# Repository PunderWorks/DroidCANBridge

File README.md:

# DroidCANBridge

A very small, inexpensive CAN-to-UART bridge for droid builders: it translates CAN bus frames to a
standard UART and back, so droid components without CAN support can join a CAN network.

- **MCU:** STM32C092 (TSSOP-20), with a built-in CAN FD controller
- **CAN:** CAN FD-capable transceiver (classic CAN 2.0 in firmware for now); two 3-pin JST-XH connectors
  (1 GND, 2 CANL, 3 CANH, the PunderWorks CAN standard) for daisy-chaining, and a jumper for the 120 Ω
  termination resistor. The CAN ground wire is optional; on the board it reaches GND through a
  resettable fuse, so it can never carry a load's return current
- **UART:** 2-pin JST-XH connector (RX, TX) with a jumper that sets the logic level to 3.3 V or 5 V
- **Power:** 5 V in on a WAGO terminal (reverse-polarity protected), with a WAGO passthrough output
- **Programming:** standard 6-pin FTDI header using the STM32's built-in serial bootloader, with
  DTR auto-reset and a boot button

Status: PCB complete (50 x 40 mm, two layers): routed, silkscreen and graphics done (PunderWorks
logo and a QR code to this repo on the back); not yet ordered. Gerbers, drills, BOM and placement
are in [`PCB/production/`](PCB/production/). Hardware is in [`PCB/`](PCB/) (see
[PCB/README.md](PCB/README.md) for requirements and design decisions); firmware will live in `src/`.

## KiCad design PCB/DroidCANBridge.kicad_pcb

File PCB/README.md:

# DroidCANBridge hardware

The electrical design is Stackup KDL in [`stackup/`](stackup/) (`board.kdl`, plus the local parts in
`parts.kdl`). The KiCad board `DroidCANBridge.kicad_pcb` is synced from it through
`DroidCANBridge.stackup_sch`. Manufacturer datasheets are in [`datasheets/`](datasheets/), with
their source URLs and hashes in `datasheets/manifest.json`.

```sh
stackup check PCB/stackup/board.kdl --locked     # check the design
```

After changing the KDL, use **Sync PCB from stackup** in KiCad's PCB editor, or sync headless with
the board closed:

```sh
/Applications/KiCad/KiCad.app/Contents/Frameworks/Python.framework/Versions/Current/bin/python3 \
  <stackup checkout>/kicad-plugin/sync_headless.py PCB/DroidCANBridge.kicad_pcb
```

Commit the synced PCB with the KDL. CI fails if syncing would change the committed PCB.

## Requirements

| Area | Requirement |
|---|---|
| Size | As small as possible. M3 mounting holes. No target outline. |
| Assembly | SMD parts assembled by JLCPCB. Connectors, terminals and headers are through-hole, hand-soldered. |
| MCU | Inexpensive STM32 with a CAN FD controller. |
| CAN | PunderWorks CAN standard (reference design DroidPowerSense v1): two 3-pin JST-XH connectors (daisy-chain in/out), pinout `1 CAN_GND, 2 CANL, 3 CANH`, printed on the silkscreen. CAN_GND to board GND through a PTC. Jumper-selectable 120 Ω termination. No power on the CAN connector. No ESD protection beyond the transceiver's own. |
| UART | One 2-pin JST-XH connector, pinout `RX, TX` (named from this board's side). Works with 3.3 V and 5 V devices, selected by a pin jumper. |
| Power | 5 V in on a through-hole WAGO terminal, with reverse-polarity protection. A second WAGO terminal passes the 5 V input through to the connected device. No fuse. |
| Programming | Standard 6-pin FTDI header (`GND, CTS, VCC, TX, RX, DTR`) on the STM32 system-bootloader UART. The board can run from the FTDI header's VCC on the bench. DTR drives reset. A small boot button selects the bootloader. |
| Indicators | None (status is reported over serial). |

## Circuit

| Block | Parts | Notes |
|---|---|---|
| Power in | J_PWR_IN, J_PWR_OUT (WAGO 2601-1102), D_IN, D_FTDI (SS14), C_VSYS | The two SS14s OR the WAGO input and the FTDI VCC onto VSYS. D_IN is the reverse-polarity protection. Each diode stops one source back-feeding the other, so the FTDI never powers the passthrough terminal. |
| 3.3 V | ldo (AP2112K-3.3) | VSYS → +3V3 for everything on the board. |
| MCU | mcu (STM32C092FCP6, TSSOP-20) | 100 nF + 4.7 µF on VDD; 100 nF NRST filter. |
| CAN | can_xcvr (TCAN334GDR), J_CAN1/J_CAN2, F_CAN_GND, R_TERM + J_TERM | STB/SHDN left on their internal pull-downs (normal mode). Connectors: pin 1 CAN_GND, 2 CANL, 3 CANH. CAN_GND runs straight from J_CAN1 to J_CAN2 (the bus ground daisy-chains) and reaches board GND through F_CAN_GND (Bourns MF-NSMF020X-2, 1206). Fit the TERM shunt at the ends of the bus. |
| Device UART | J_UART, J_VIO, R_TXPU, Q_RX (BSS138), R_RXPU | TX: open-drain with a 1 kΩ pull-up to the jumper-selected level. RX: BSS138 level shifter. |
| FTDI | J_FTDI, C_DTR, D_NRST (BAT54S) | DTR is AC-coupled to NRST (Arduino-style auto-reset); the BAT54S clamps NRST between GND and +3V3. CTS is tied to GND. |
| Boot | SW_BOOT (TS-1187A), R_BOOT | Hold SW_BOOT through a reset to enter the bootloader. No SWD pads: the FTDI header is the only programming path. |

Jumpers: **J_VIO** shunt on 1-2 = 3.3 V UART, 2-3 = 5 V UART (VSYS). **J_TERM** shunt fitted = 120 Ω
terminator in. The two shunts (SH_VIO, SH_TERM: Würth 60900213421) are BOM-only parts with
outline-only footprints, so they are on the BOM but not in the placement file.

## Layout

The board is 50 x 40 mm, two layers, laid out for how it sits in a droid harness, with
power and signals flowing left to right:

| Edge | Connectors |
|---|---|
| Left (in) | J_PWR_IN (WAGO, wires enter from the left), J_CAN1 |
| Right (out) | J_PWR_OUT (WAGO, wires leave to the right), J_CAN2, J_UART |
| Bottom | J_FTDI, lying along the edge, pin 1 (GND) on the left |

- Both WAGOs have **+5V on the top pole and GND on the bottom**. J_PWR_OUT is turned the opposite
  way from J_PWR_IN, which reverses its pin order, so its +5V is pin 2 (see `board.kdl`). Mark + and
  − on the silkscreen beside both.
- The CAN connectors are turned opposite ways: J_CAN1 reads CANH, CANL, CAN_GND from the top
  (pin 1 at the bottom) and J_CAN2 reads CAN_GND, CANL, CANH (pin 1 at the top). Each pin has an
  edge label (H, L, G) beside it. J_UART has pin 1 (RX) at the top.
- J_CAN2 sits between the 5V OUT WAGO and J_UART, with 1.1 mm and 1.4 mm between the bodies, so its
  "CAN OUT" label runs vertically to its left (0.8 mm-wide characters, as on the FTDI pins).
- CAN_GND: J_CAN1 pin 1 to F_CAN_GND (beside TERM) on the top, and a 0.5 mm track on the bottom
  from J_CAN1 pin 1, under the FTDI header, up to J_CAN2 pin 1. F_CAN_GND's other pad joins the
  top GND pour.
- The +5V passthrough runs straight across the top edge between the WAGOs, above the OR diodes and
  LDO. Size it for the passthrough current, not the board's own < 100 mA.
- The WAGO levers overhang the side edges by about 2 mm (WAGO drawing: 16.58 mm with the lever
  against the 14.5 mm body).
- Two M3 holes in opposite corners: H1 bottom-left, H2 top-right (above J_PWR_OUT). Each has a
  3.5 mm-radius copper keep-out on both layers (rule areas `Keepout H1/H2`), so screw heads,
  washers and standoffs sit on bare board, not on the GND pour.
- GND pours fill both layers. The bottom one gives the passthrough's return a solid path under the
  3 mm +5V_IN track. Pads join them through thermal reliefs with 0.5 mm spokes, wide enough for the
  WAGO GND pins and still easy to hand-solder. 26 GND stitching vias (0.8/0.4 mm) around the
  perimeter and through open areas tie the two pours together, plus vias joining top-pour pockets
  that tracks enclose.
- Silkscreen: reference designators and values are hidden (they remain on the Fab layer for
  assembly drawings). The top labels each connector, jumper setting and the boot button, and the
  FTDI pins from the cable's side (GND, CTS, VCC, RXI, TXO, DTR). The back carries the PunderWorks
  logo (`PunderWorks_Logo_14mm`, a board-only footprint in `libraries/DroidCANBridge.pretty`,
  copied from DroidPowerSense with its source image in `libraries/logos/`), the board name and
  version, the repo URL, and a 6.2 mm QR code to github.com/PunderWorks/DroidCANBridge.
- `scripts/pcb/place.py` produced the starting placement. Once the board is edited in KiCad, the
  board file is the source of truth.

## GPIO table (STM32C092FCP6, TSSOP-20)

From DS14720 Rev 2, Figure 3 and Table 12. Pads marked "shared" bond several die pins together;
firmware must leave the unused ones in their reset (analog) state.

| Pad | Pin (shared) | Net | Function | Notes |
|---|---|---|---|---|
| 1 | PB7 (PB8) | UART_RX_3V3 | USART1_RX | From Q_RX; 1 kΩ pull-up on board. |
| 2 | PC14 | — | spare | |
| 3 | PC15 | — | spare | |
| 4 | VDD/VDDA | +3V3 | supply | |
| 5 | VSS/VSSA | GND | supply | |
| 6 | PF2-NRST | NRST | reset | Bidirectional reset (factory NRST_MODE = 11). DTR auto-reset. |
| 7, 8 | PA0, PA1 | — | spare | |
| 9 | PA2 | FTDI_RXD | USART2_TX | Bootloader USART (AN2606 Table 19). |
| 10 | PA3 | FTDI_TXD | USART2_RX | Bootloader USART. |
| 11-14 | PA4-PA7 | — | spare | Bootloader SPI1 pins (pulled down in bootloader mode); unused here. |
| 15 | PA8 (PB0, PB1, PB2) | — | spare | |
| 16 | PA11 (PA9) | CAN_RX | FDCAN1_RX | Bootloader remaps USART1_TX here but holds it in reset state until 0x7F arrives on pad 17. |
| 17 | PA12 (PA10) | CAN_TX | FDCAN1_TX | Bootloader remaps USART1_RX here (input, pull-up). Only the transceiver's TXD input is on it. |
| 18 | PA13 | — | spare (SWDIO) | Not brought out; no SWD on this board. |
| 19 | PA14-BOOT0 (PA15) | BOOT0 | BOOT0 | 10 kΩ pull-down + SW_BOOT to +3V3. BOOT0 only once nBOOT_SEL is cleared (see Firmware). |
| 20 | PB6 (PB3, PB4, PB5) | UART_TX | USART1_TX | Open-drain, internal pull off (pin sees up to 5.25 V). Bootloader I2C1_SCL. |

## DC operating points

Supply states: WAGO only, FTDI only, both, and the bridge unpowered with the UART device powered.

| Node | Value | Limit (source) | OK |
|---|---|---|---|
| +5V_IN | 4.75-5.25 V (stated ±5%) | SS14 VRRM 40 V | ✓ |
| FTDI_VCC | 4.4-5.25 V (USB at the device) | SS14 VRRM 40 V | ✓ |
| VSYS | 3.85-5.25 V (input less ≤ 0.55 V, SS14 VF at 1 A; < 0.4 V typical at this current) | AP2112 VIN 2.5-6 V; needs ≥ 3.5 V (3.3 V + 200 mV max dropout at 300 mA, AP2112 table p. 8) | ✓ |
| +3V3 | 3.25-3.35 V (±1.5%) | STM32 2.0-3.6 V; TCAN334 3.0-3.6 V | ✓ |
| +3V3 load | ≤ 85 mA (TCAN334 70 mA dominant + MCU budget 15 mA) | AP2112 600 mA | ✓ |
| LDO dissipation | ≤ (5.25 - 3.25) V × 85 mA = 0.17 W | SOT-23-5; check the board temperature on the bench | ✓ |
| UART_TX low | sinking ≤ 5.25 mA (VIO / 1 kΩ) | VOL ≤ 0.4 V at 8 mA (DS14720 Table 51) | ✓ |
| UART_TX high, 5 V setting | 3.85-5.25 V | ATmega VIH 0.6 × VCC = 3.0 V at 5 V (from memory, typical AVR); PB6 FT max VDD + 4.0 V = 7.25 V (Table 21) | ✓ |
| Q_RX on (device TX low ≤ 0.8 V) | VGS ≥ 3.25 - 0.8 = 2.45 V | BSS138 VGS(th) max 1.5 V (onsemi, electrical characteristics) | ✓ |
| UART_RX_3V3, device low | ≤ 0.8 V + 3.3 mA × RDS(on) (≤ 6 Ω at 4.5 V; more at 2.45 V) ≈ 0.85 V | VIL 0.3 × VDD = 0.98 V (Table 50) | ✓ (assumes device VOL ≤ 0.8 V; typical ≤ 0.4 V) |
| UART_RX_3V3, device high | 3.25 V via R_RXPU | VIH 0.7 × VDD = 2.31 V | ✓ |
| UART_RX_3V3, bridge unpowered | ≈ 0 V (FET off, body diode reverse-biased) | FT pin max 4.0 V with VDD = 0 (Table 21) | ✓ |
| BOOT0 at rest / pressed | 0 V / 3.3 V (0.33 mA) | VIL 0.98 V / VIH 2.31 V | ✓ |
| NRST on DTR fall, 3.3 V cable | 3.3 - 3.3 × 1 µF/1.1 µF = 0.3 V, below VIL for 7-16 ms (τ = 1.1 µF × RPU 25-55 kΩ) | VIL(NRST) 0.3 × VDD = 0.98 V; filter 70 ns (Table 53) | ✓ |
| NRST on DTR fall, 5 V cable | clamped by BAT54S to -0.35 to -0.52 V, below VIL for 12-27 ms (SPICE) | MCU negative injection ≤ 5 mA (Table 22): simulated ≤ 0.25 mA; without the BAT54S, 26 mA | ✓ |
| NRST on DTR rise (port close) | ≤ 4.32 V with the BAT54S (SPICE); 7.9 V without it | VIN ≤ VDD + 4.0 V = 7.3 V (Table 21) | ✓ |
| CAN terminator | 2-3 V differential across 120 Ω → ≤ 75 mW | 0805 125 mW | ✓ |
| CAN_GND to GND, normal | ~0 A (≈ 1 mA signal reference at most), ≤ 3.3 Ω (R1max) → ≤ 3.3 mV | Ihold 0.20 A at 23 °C, 0.10 A at 85 °C (MF-NSMF pp. 1, 3) | ✓ |
| CAN_GND to GND, fault | WAGO GND lost with a CAN cable fitted: this board's < 100 mA plus the passthrough load's return (≤ 10 A, the WAGO rating; no upstream fuse) through the PTC until it trips; then ~0.6 W tripped at ≤ 5.25 V | Vmax 30 V (5.7× the 5.25 V max), Imax 60 A, trips in ≤ 0.6 s at 1.0 A (MF-NSMF p. 1); JST-XH contact 3 A | ✓ |

## Firmware requirements from the hardware

- **First flash: clear nBOOT_SEL over the UART before writing any firmware.** Factory option bytes
  are nBOOT_SEL = 1, nBOOT0 = 1 (RM0490 p. 66), so a fresh part ignores the BOOT0 pin and reaches
  the bootloader only through the empty-flash check (RM0490 Table 9, §3.1.4). There are no SWD pads,
  so if firmware were written first with nBOOT_SEL still set, the chip would always boot from flash
  and only that firmware could get back to the bootloader. On the blank chip, connect the FTDI
  and run `STM32_Programmer_CLI -c port=<tty> -ob nBOOT_SEL=0` (STM32CubeProgrammer talks to the ROM
  bootloader over UART and can write option bytes). From then on, holding SW_BOOT through a reset
  always reaches the bootloader, whatever the firmware does. Firmware should also check the bit at
  startup and clear it if a board somehow skipped the step.
- **PB6 (UART TX):** open-drain alternate function, internal pull-up and pull-down off (required to
  sustain more than 4 V, DS14720 Table 21 note 2).
- **PB7 (UART RX):** no internal pull needed (R_RXPU).
- **FDCAN (PunderWorks CAN standard):** classic CAN 2.0 frame format with FD mode off, not just a
  matching data rate, and payloads of at most 8 bytes. One bit rate across the bus, set by the
  motor controllers, with the sample point at ~87.5% (match it on every node). Enable protocol
  exception handling too, so a stray FD frame is ignored instead of answered with error frames.
  The hardware stays FD-capable, so a later move to FD is firmware and segmenting only.
- **Shared pads:** leave PB8, PB0-PB2, PA9, PA10, PA15, PB3-PB5 untouched (analog). Use the SYSCFG
  remap only if the pad assignment changes.
- **Flashing:** the ROM bootloader on USART2 (8 data bits, even parity, 1 stop bit; AN2606 Table 19).
  Hold SW_BOOT, let the flasher pulse DTR, release after it connects.

## Decisions

- **STM32C092FCP6 (TSSOP-20).** The cheapest STM32 with FDCAN (the C091 has none). No STM32 comes in a
  through-hole package, so the MCU is SMD; once JLCPCB is assembling it, the other small parts are SMD
  too to keep the board compact. The library part only has LQFP packages, so `parts.kdl` carries a
  TSSOP-20 copy (candidate to upstream). JLCPCB stock is low (C44847704, 6 pcs on 2026-11-05;
  Mouser 3,314), so recheck before ordering and plan on global sourcing or consigned parts.
- **Pin plan.** FTDI on USART2 PA2/PA3 because that is a bootloader USART bonded on TSSOP-20 (the other,
  USART1 on PA9/PA10, is remapped onto pads 16/17 there). CAN on pads 16/17. Device UART on USART1
  PB6/PB7 (pads 20/1). The bootloader's I2C1 on PB6/PB7 cannot trigger: SCL (PB6) never toggles with
  the MCU in the bootloader. Its FDCAN bootloader is not available on TSSOP-20 (AN2606 Table 19 note 2).
- **PunderWorks CAN standard (2026-11-17).** All PunderWorks CAN boards match DroidPowerSense v1:
  3-pin JST-XH (1 CAN_GND, 2 CANL, 3 CANH), TCAN334GDR, CAN_GND daisy-chained between the two
  connectors and tied to GND through a PTC, 120 Ω on a TERM jumper with a Würth
  60900213421 shunt, and no power on the CAN connector. This board was brought into line before
  it was ever made, so it stays V1.0. It replaces the earlier 2-pin connectors with no ground,
  which relied on every board sharing ground through the power wiring. A bus ground wire keeps
  nodes within the transceiver's common-mode range when they are powered separately. Without the
  PTC, losing this board's WAGO GND with a CAN cable still fitted would send the downstream
  device's return current through a 3 A JST contact and signal wire. The shunt is
  DroidPowerSense's. The builder may leave out the CAN_GND wire.
- **CAN_GND PTC: Bourns MF-NSMF020X-2, 1206 (2026-11-18).** The standard leaves the PTC to each
  board. DroidPowerSense's MF-MSMF014/60X-2 (60 V, 1812) is sized for a 32 V battery rail and
  isn't stocked at LCSC, so this 5 V board uses a 1206: Vmax 30 V, Imax 60 A, Ihold 0.20 A
  (0.10 A at 85 °C), R1max 3.3 Ω (MF-NSMF p. 1, p. 3). Imax covers the worst case, the passthrough
  load's return bounded only by the 10 A WAGO since there is no upstream fuse. Ihold is far
  above the ≈ 1 mA reference current and the trip current (0.40 A) well under the 3 A JST
  contact. Footprint `DroidCANBridge:Bourns_MF-NSMF_1206_Style2` from the p. 8 pad layout
  (1.0 × 1.6 mm pads, 2.0 mm gap). Stock on 2026-11-18: Mouser 11,420, DigiKey 28,416, LCSC
  9,850 (C210358, JLCPCB Extended). Rejected: MF-NSMF020 (non-X, Imax only 10 A), MF-NSMF025/24X
  (13 at LCSC), the 6 V 1206/0805 parts (too little Vmax margin over 5.25 V).
- **CAN FD hardware, classic CAN firmware first.** The bus mixes CAN FD and classic nodes. A classic
  node does not slow the others down, since every node already shares the nominal (arbitration) bit
  rate. But a strictly classic controller (e.g. MCP2515) answers FD frames with error frames. The
  STM32 FDCAN can run in classic mode and ignore FD frames (protocol exception handling), so this
  board stays safe on a mixed bus and can move to FD in firmware later. Messages addressed to the
  bridge must be sent as classic frames while it runs in classic mode.
- **TCAN334G, 3.3 V transceiver.** Running everything from 3.3 V lets the power path use plain
  Schottky diodes for OR-ing and reverse protection: a 5 V-only transceiver (MCP2562FD, VDD ≥ 4.5 V)
  would not tolerate the diode drop. This replaced the P-MOSFET reverse protection discussed earlier:
  with no 5 V load, the diode's drop costs nothing and it also does the OR-ing.
- **Firmware platform: PlatformIO + STM32duino.** `platform-ststm32` v20.0.0 has a `nucleo_c092rc`
  board (Arduino, STM32Cube, Zephyr), and STM32duino 3.0.0 has the TSSOP-20 variant
  `STM32C0xx/C092ECY_C092F(B-C)P`, so a small custom board JSON is enough. FDCAN is used through the
  bundled HAL; STM32duino has no CAN library.
- **UART level shifting.** TX: open-drain with a pull-up to the J_VIO rail, no extra parts. RX: a
  BSS138, because the FT pin's limit drops to 4.0 V with the bridge unpowered and positive injection
  is not allowed (DS14720 Tables 21-22), so a series resistor can't protect it from a separately
  powered 5 V device.
- **JST-XH** for CAN and UART (the community's preferred connector). CAN follows the PunderWorks
  standard above. The UART stays **2-pin with no ground**: the UART device is powered from this
  board's passthrough, so its ground return is short. **WAGO 2601-1102** (10 A, lever push-in,
  horizontal entry) for power.

## Accepted risks and known gaps

- **Passthrough is unprotected.** J_PWR_OUT is wired to the input terminal, so reversed input reaches
  the downstream device. D_IN protects only this board.
- **Reversed power with other grounds connected.** If the input is reversed while the UART device's
  ground is tied to the system ground, current flows through the board's ground copper; no series
  part can stop that. Through a CAN ground wire, F_CAN_GND trips and limits it to tens of mA.
- **FTDI adapters with 3.3 V on VCC.** Some adapters supply 3.3 V instead of 5 V on the VCC pin.
  VSYS is then about 3.0 V, the LDO drops out to about 2.8 V, and the TCAN334G (3.0 V minimum)
  is out of spec. Flashing still works (the STM32 runs from 2.0 V); CAN needs the WAGO input.
- **FTDI adapter without VCC wired.** If an adapter drives 5 V TX into PA3 without supplying VCC and
  nothing else powers the board, PA3 exceeds its 4.0 V unpowered limit. Normal FTDI cables supply
  VCC.
- **UART ground shares the power wiring.** If the UART device's ground also carries heavy load
  current (a motor controller, say), the offset appears in the UART signal levels. Fine for a device
  powered from J_PWR_OUT; worth checking for anything else.
- **J_VIO with no shunt** leaves UART TX without a pull-up (the device's RX floats). Always fit a shunt.
- **`stackup bom` reports 2 parts without an MPN:** the two mounting holes, which are drill only
  with nothing to buy.
- **No SWD access.** Programming and recovery go through the FTDI header and the ROM bootloader
  only, which relies on nBOOT_SEL being cleared at the first flash (see Firmware requirements).
- **AP2112 θJA for SOT-23-5** was not found in the datasheet text; 0.17 W worst case is small but the
  LDO temperature is on the bench checklist.

## Final review (2026-11-05)

Pre-fab review of the routed board at `ede7f2c`. Clean: `stackup check` (0/0/0), PCB sync check,
DRC with zones refilled (0 violations, 0 unconnected), footprint pad numbers against every IC
and diode datasheet pin table, silkscreen labels against the nets they name, the saved zone fill
(identical to a refill), JLC trace/space, via, annular-ring and hole-spacing limits
(`datasheets/JLC-PCB-capabilities.txt`), and the DTR reset simulation (`scripts/spice/`).

Fixed in the review: hole keep-outs, 26 stitching vias, back silkscreen "rev A" → "V1.0" (the
board's version, matching the front), UART label "SERIAL IN" → "SERIAL". U3 moved up and C7 (its
100 nF) moved beside it: 3.0 mm of track to VCC (was 6.2 mm) and 2.8 mm to GND, with the supply
reaching C7 before U3, per TI's "as close to the VCC supply pins as possible" (TCAN334 §7.4).

Decoupling arrangement, traced along the copper: C4 (MCU VDD) and C7 (TCAN VCC) are in line
between the supply and the pin; C1 (VSYS bulk) sits where both OR diodes meet; C6 is 3.0 mm from
NRST; the BAT54S clamp sits at C8 where the DTR surge enters. The regulator's own caps hang off
short branches: C3 (output) 6.9 mm from VOUT and C2 (input) 8.7 mm from VIN. Accepted: the
AP2112 is stable with 1 µF ceramics and C1's 4.7 µF is in line on the input.

Silkscreen: every board text is at least 1.0 mm tall (JLC's minimum, "characters height less than
40 mil (1.0 mm) will be unidentifiable"), and the board setup's minimum text height is 1.0 mm so
DRC enforces it. The FTDI pin names are 1.0 mm tall by 0.8 mm wide to fit the 2.54 mm pitch. The
edge labels beside the WAGO and JST pins are one text per pin, placed at that pin.

Accepted findings:
- `bom_check.py` flags H1/H2 for no MPN or LCSC: they are drill-only, nothing to buy.
- The WAGO "5V / G" edge labels sit between each terminal and the board edge, under the
  overhanging levers: hidden from directly above, visible at an angle and with the levers open.
  The back pinout legend that repeated the polarity was replaced by the logo and QR code
  (2026-11-08), so the edge labels are now the only polarity marking.
- KiCad's stock footprints draw silkscreen at 0.12 mm, under JLC's 0.15 mm line minimum. Common
  practice; outlines may print faint. Not changed.

## CAN standard update (2026-11-17)

Brought in line with the PunderWorks CAN standard (see Decisions): J_CAN1/J_CAN2 to 3-pin, F_CAN_GND
added, SH_TERM/SH_VIO in the BOM. Re-checked after the change: `stackup check` 0/0/0 (33 parts,
20 nets), PCB sync check clean, DRC with zones refilled 0 violations and 0 unconnected, F1 pads
against Bourns p. 7. To make room, two GND stitching vias moved off F1's pads and two off the new
edge labels. Fab files and the renders in `assets/` regenerated.

## Fab files

[`production/`](production/) holds the Gerbers and job file (2 layers, 1.6 mm) and the PTH/NPTH
drills with maps in `production/gerbers/`, and the purchasing BOM (`stackup bom`, with LCSC numbers
for JLCPCB) and the placement file in `production/bom/`. The placement file lists only the 21
JLCPCB-placed parts: the hand-soldered connectors and headers (J1-J8) and the loose jumper shunts
(SH1, SH2) are `hand=#true` in the KDL,
which marks them Hand/DNP in the BOM and, from Stackup 0.3.0, makes the PCB sync give their
footprints KiCad's *Exclude from position files* and *Exclude from BOM* attributes. The mounting
holes' stock footprint carries both attributes itself. Check JLCPCB's placement preview for rotation and pin 1 on U1-U3, Q1, D1-D3 and SW1.
F1 has no LCSC number (see Accepted risks): order it through global sourcing or consign it.

Regenerate everything after any board change. Refill and save the pours first, because the
exporters plot the fills stored in the board file:

```sh
K=/Applications/KiCad/KiCad.app/Contents/MacOS/kicad-cli; B=PCB/DroidCANBridge.kicad_pcb
$K pcb drc --refill-zones --save-board --severity-all -o /tmp/drc.rpt $B   # refill, save, and check
$K pcb export gerbers --board-plot-params -o PCB/production/gerbers/ $B
$K pcb export drill --excellon-separate-th --generate-map --map-format gerberx2 -o PCB/production/gerbers/ $B
$K pcb export pos --format csv --units mm --side both --exclude-dnp -o PCB/production/bom/DroidCANBridge-pos.csv $B
stackup bom PCB/stackup/board.kdl --locked -o PCB/production/bom/DroidCANBridge-bom.csv
```

`stackup bom` exits 1 because H1/H2 have no MPN (see accepted findings) but still writes the CSV.
The placement file needs no hand editing: the footprint attributes already keep J1-J8, SH1/SH2
and H1/H2 out of it.

## Bench checklist (first board)

1. Before power: inspect U1/U2/U3 orientation, D_IN/D_FTDI bands (cathode toward VSYS), D_NRST and
   Q1 orientation.
2. Current-limited 5 V on J_PWR_IN (limit ~150 mA): VSYS ≈ 4.6-4.8 V, +3V3 = 3.25-3.35 V, idle
   current noted. Reverse the input briefly: no current, board stays dead.
3. FTDI only: board powers, J_PWR_IN/J_PWR_OUT stay at 0 V (no back-feed).
4. Blank chip: confirm it enters the bootloader (empty check) and `stm32flash` talks on USART2.
   Confirm DTR produces a reset (scope NRST: a ~10-20 ms low pulse, no excursion beyond -0.4 V or
   +3.7 V with a 5 V cable).
5. Clear nBOOT_SEL with STM32CubeProgrammer over the FTDI; then confirm hold-SW_BOOT + DTR reset
   enters the bootloader, before and after flashing firmware.
6. CAN: CANH/CANL recessive ≈ 2.5 V, 120 Ω between them with J_TERM fitted (60 Ω with both ends
   terminated). Exchange classic frames with a known node (DroidPowerSense) at the motor
   controllers' bit rate and an 87.5% sample point; confirm no error frames when an FD node
   transmits FD frames. Confirm the pinout against DroidPowerSense with one cable: pin 1 GND on
   both ends.
7. CAN_GND: continuity J_CAN1.1 to J_CAN2.1 (direct), and to GND through F_CAN_GND (≤ 6 Ω). With
   the WAGO GND disconnected and a load returning through a CAN cable's ground, F_CAN_GND trips and
   the current falls to mA.
8. UART: loopback at 3.3 V and 5 V settings; scope TX rise time at the target baud rate; with the
   bridge unpowered and a powered 5 V device on J_UART, confirm PB7 stays ≈ 0 V.
9. LDO temperature with the CAN bus heavily loaded.

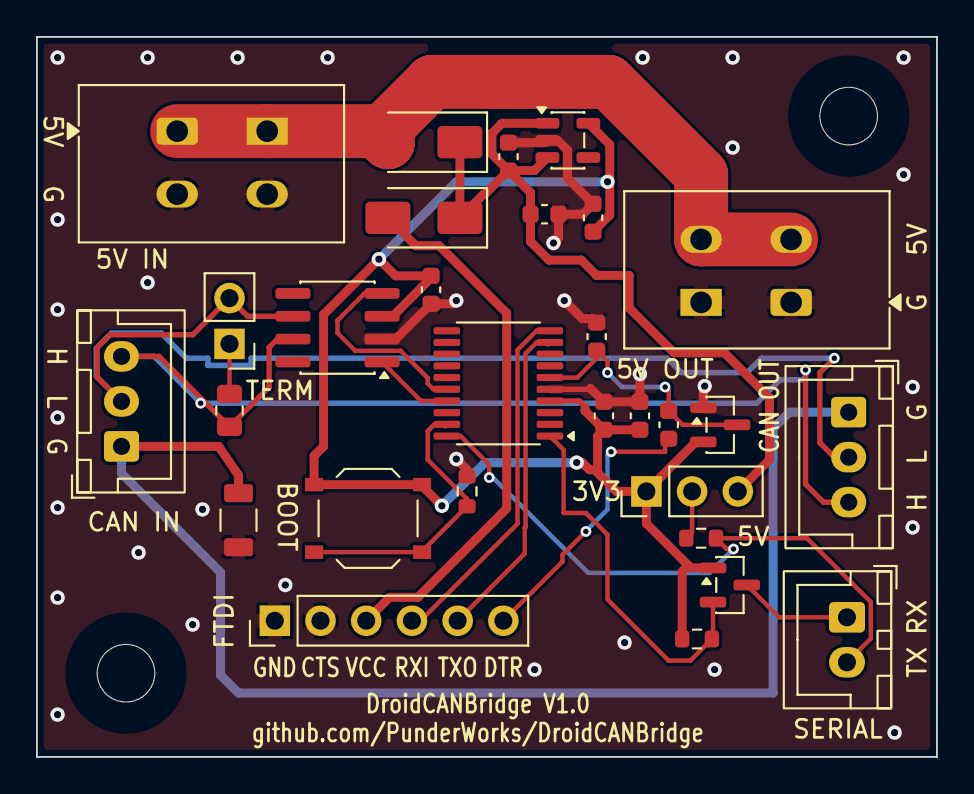
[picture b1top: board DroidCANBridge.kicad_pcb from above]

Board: 2 copper layers, 50.0 x 40.0 mm, 34 parts (1 on the bottom side), 20 nets.

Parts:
C1, C5: 4.7µF; C_0603_1608Metric
C2, C3, C8: 1µF; C_0603_1608Metric
C4, C6, C7: 100nF; C_0603_1608Metric
D1, D2: SS14; D_SMA
D3: BAT54S; SOT-23
F1: MF-NSMF020X-2; Bourns_MF-NSMF_1206_Style2
H1, H2: MountingHole; MountingHole_3.2mm_M3
J1, J2: WAGO 2601-1102; WAGO_2601-1102_Horizontal
J3, J4: JST XH 3-pin; JST_XH_B3B-XH-A_1x03_P2.50mm_Vertical
J5: TERM; PinHeader_1x02_P2.54mm_Vertical
J6: JST XH 2-pin; JST_XH_B2B-XH-A_1x02_P2.50mm_Vertical
J7: 3V3 | VIO | 5V; PinHeader_1x03_P2.54mm_Vertical
J8: FTDI; PinHeader_1x06_P2.54mm_Vertical
LOGO**: PunderWorks_Logo_14mm
Q1: BSS138; SOT-23
R1: 120Ω; R_0805_2012Metric
R2, R3: 1kΩ; R_0603_1608Metric
R4: 10kΩ; R_0603_1608Metric
SH1, SH2: Jumper shunt for 2.54mm PinHeader; BOM_Only_JumperShunt
SW1: TS-1187A-B-A-B; XKB_TS-1187A-B-A-B
U1: AP2112K-3.3; SOT-23-5
U2: STM32C092FxPx; TSSOP-20_4.4x6.5mm_P0.65mm
U3: TCAN334G; SOIC-8_3.9x4.9mm_P1.27mm

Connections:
+3V3: C3.1, C4.1, C5.1, C7.1, D3.2, J7.1, Q1.1, R3.2, SW1.1, U1.5, U2.4, U3.3
+5V_IN: D1.2, J1.1, J2.2
BOOT0: R4.1, SW1.2, U2.19
CANH: J3.3, J4.3, R1.1, U3.7
CANL: J3.2, J4.2, J5.2, U3.6
CAN_GND: F1.1, J3.1, J4.1
CAN_RX: U2.16, U3.4
CAN_TX: U2.17, U3.1
FTDI_DTR: C8.1, J8.6
FTDI_RXD: J8.5, U2.9
FTDI_TXD: J8.4, U2.10
FTDI_VCC: D2.2, J8.3
GND: C1.2, C2.2, C3.2, C4.2, C5.2, C6.2, C7.2, D3.1, F1.2, J1.2, J2.1, J8.1, J8.2, R4.2, U1.2, U2.5, U3.2
NRST: C6.1, C8.2, D3.3, U2.6
unnamed: J5.1, R1.2
UART_RX: J6.1, Q1.3
UART_RX_3V3: Q1.2, R3.1, U2.1
UART_TX: J6.2, R2.2, U2.20
UART_VIO: J7.2, R2.1
VSYS: C1.1, C2.1, D1.1, D2.1, J7.3, U1.1, U1.3

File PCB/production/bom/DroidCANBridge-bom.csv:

Refs,Quantity,Value,Footprint,MF,MPN,LCSC,Mouser,DigiKey,Hand,DNP
"C4,C6,C7","3","100nF","Capacitor_SMD:C_0603_1608Metric","YAGEO","CC0603KRX7R9BB104","C14663","","","",""
"R4","1","10kΩ","Resistor_SMD:R_0603_1608Metric","UNI-ROYAL","0603WAF1002T5E","C25804","","","",""
"R1","1","120Ω","Resistor_SMD:R_0805_2012Metric","UNI-ROYAL","0805W8F1200T5E","C17437","","","",""
"R2,R3","2","1kΩ","Resistor_SMD:R_0603_1608Metric","UNI-ROYAL","0603WAF1001T5E","C21190","","","",""
"C2,C3,C8","3","1µF","Capacitor_SMD:C_0603_1608Metric","Samsung Electro-Mechanics","CL10A105KB8NNNC","C15849","","","",""
"J7","1","3V3 | VIO | 5V","Connector_PinHeader_2.54mm:PinHeader_1x03_P2.54mm_Vertical","XFCN","PZ254V-11-03P","C2937625","","","Yes","Yes"
"C1,C5","2","4.7µF","Capacitor_SMD:C_0603_1608Metric","Samsung Electro-Mechanics","CL10A475KO8NNNC","C19666","","","",""
"U1","1","AP2112K-3.3","Package_TO_SOT_SMD:SOT-23-5","Diodes Incorporated","AP2112K-3.3TRG1","C51118","621-AP2112K-3.3TRG1","","",""
"D3","1","BAT54S","Package_TO_SOT_SMD:SOT-23","MDD (Microdiode Semiconductor)","BAT54S","C408389","","","",""
"Q1","1","BSS138","Package_TO_SOT_SMD:SOT-23","onsemi","BSS138","C52895","","","",""
"J8","1","FTDI","Connector_PinHeader_2.54mm:PinHeader_1x06_P2.54mm_Vertical","XFCN","PZ254V-11-06P","C492405","","","Yes","Yes"
"J6","1","JST XH 2-pin","Connector_JST:JST_XH_B2B-XH-A_1x02_P2.50mm_Vertical","JST","B2B-XH-A(LF)(SN)","C158012","","","Yes","Yes"
"J3,J4","2","JST XH 3-pin","Connector_JST:JST_XH_B3B-XH-A_1x03_P2.50mm_Vertical","JST","B3B-XH-A(LF)(SN)","C144394","306-B3BXHALFSNP","","Yes","Yes"
"SH1,SH2","2","Jumper shunt for 2.54mm PinHeader","DroidCANBridge:BOM_Only_JumperShunt","Würth Elektronik","60900213421","C6823945","710-60900213421","732-2678-ND","Yes","Yes"
"F1","1","MF-MSMF014/60X-2","DroidCANBridge:Bourns_MF-MSMF_1812_Style2","Bourns","MF-MSMF014/60X-2","","652-MF-MSMF014/60X-2","118-MF-MSMF014/60X-2CT-ND","",""
"H1,H2","2","MountingHole","MountingHole:MountingHole_3.2mm_M3","","","","","","",""
"D1,D2","2","SS14","Diode_SMD:D_SMA","MDD (Microdiode Semiconductor)","SS14","C2480","","","",""
"U2","1","STM32C092FxPx","Package_SO:TSSOP-20_4.4x6.5mm_P0.65mm","STMicroelectronics","STM32C092FCP6","C44847704","511-STM32C092FCP6","","",""
"U3","1","TCAN334G","Package_SO:SOIC-8_3.9x4.9mm_P1.27mm","Texas Instruments","TCAN334GDR","C189939","595-TCAN334GDR","","",""
"J5","1","TERM","Connector_PinHeader_2.54mm:PinHeader_1x02_P2.54mm_Vertical","XFCN","PZ254V-11-02P","C492401","","","Yes","Yes"
"SW1","1","TS-1187A-B-A-B","DroidCANBridge:XKB_TS-1187A-B-A-B","XKB Connection","TS-1187A-B-A-B","C318884","","","",""
"J1,J2","2","WAGO 2601-1102","DroidCANBridge:WAGO_2601-1102_Horizontal","WAGO","2601-1102","C7509568","","","Yes","Yes"
